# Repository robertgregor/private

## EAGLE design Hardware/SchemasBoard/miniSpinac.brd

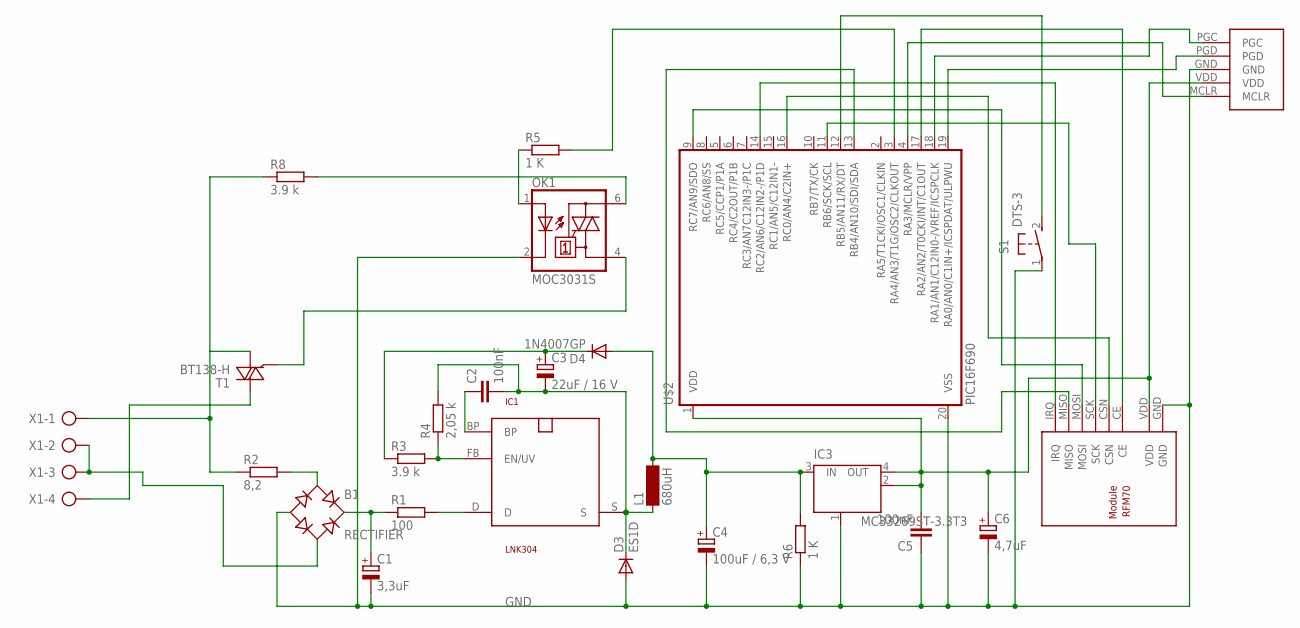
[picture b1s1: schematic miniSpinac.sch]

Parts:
B1: RECTIFIER; TO-269AA
C1: 3,3uF; E5-10,5
C2, C5: 100nF; C2012
C3: 22uF / 16 V; SMC_C
C4: 100uF / 6,3 V; E2,5-5
C6: 4,7uF; SMC_A
D3: ES1D; DO214AC
D4: 1N4007GP; DO214AA
IC1: LNK304; SO-8C
IC3: MC33269ST-3.3T3; SOT223
L1: 680uH; BS11
OK1: MOC3031S; DIL6-SMD
R1: 100; R2512W
R2: 8,2; 0411/12
R3, R8: 3.9 k; M2012
R4: 2,05 k; M2012
R5, R6: 1 K; M2012
S1: DTS-3
T1: BT138-H; TO220BH
U$1: RFM70
U$2: PIC16F690; SSOP20
U$3: PROGRAMMINGHEADERDIP; PROGHEADER
X1: AK500/4

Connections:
GND: B1.-, C1.-, C4.-, C5.1, C6.-, D3.A, IC3.1 (GND/ADJ), OK1.2 (C), R6.1, S1.1, U$1.GND, U$2.20 (VSS), U$3.GND
unnamed: IC1.D, R1.2
unnamed: B1.+, C1.+, R1.1
unnamed: B1.AC1, R2.2
unnamed: B1.AC2, X1.2, X1.3
unnamed: S1.2, U$2.12 (RB5/AN11/RX/DT)
unnamed: T1.T2 (A2), X1.4
unnamed: OK1.1 (A), R5.1
unnamed: OK1.4 (A1), T1.G
unnamed: C3.+, D4.C, R3.1
unnamed: C2.1, IC1.BP
unnamed: IC1.FB (EN/UV), R3.2, R4.1
unnamed: U$1.MISO, U$2.13 (RB4/AN10/SDI/SDA)
unnamed: C2.2, C3.-, D3.C, IC1.S, L1.1, R4.2
unnamed: OK1.6 (A2), R8.2
unnamed: U$1.CE, U$2.17 (RA2/AN2/T0CKI/INT/C1OUT)
unnamed: U$2.19 (RA0/AN0/C1IN+/ICSPDAT/ULPWU), U$3.PGD
unnamed: U$2.18 (RA1/AN1/C12IN0-/VREF/ICSPCLK), U$3.PGC
unnamed: U$1.CSN, U$2.16 (RC0/AN4/C2IN+)
unnamed: U$1.IRQ, U$2.14 (RC2/AN6/C12IN2-/P1D)
unnamed: U$1.SCK, U$2.11 (RB6/SCK/SCL)
unnamed: U$1.MOSI, U$2.9 (RC7/AN9/SDO)
unnamed: U$2.4 (RA3/MCLR/VPP), U$3.MCLR
unnamed: C4.+, D4.A, IC3.3 (IN), L1.2, R6.2
unnamed: C5.2, C6.+, IC3.2 (OUT), IC3.4 (OUT), U$1.VDD, U$2.1 (VDD), U$3.VDD
unnamed: R5.2, U$2.3 (RA4/AN3/T1G/OSC2/CLKOUT)
unnamed: R2.1, R8.1, T1.T1 (A1), X1.1

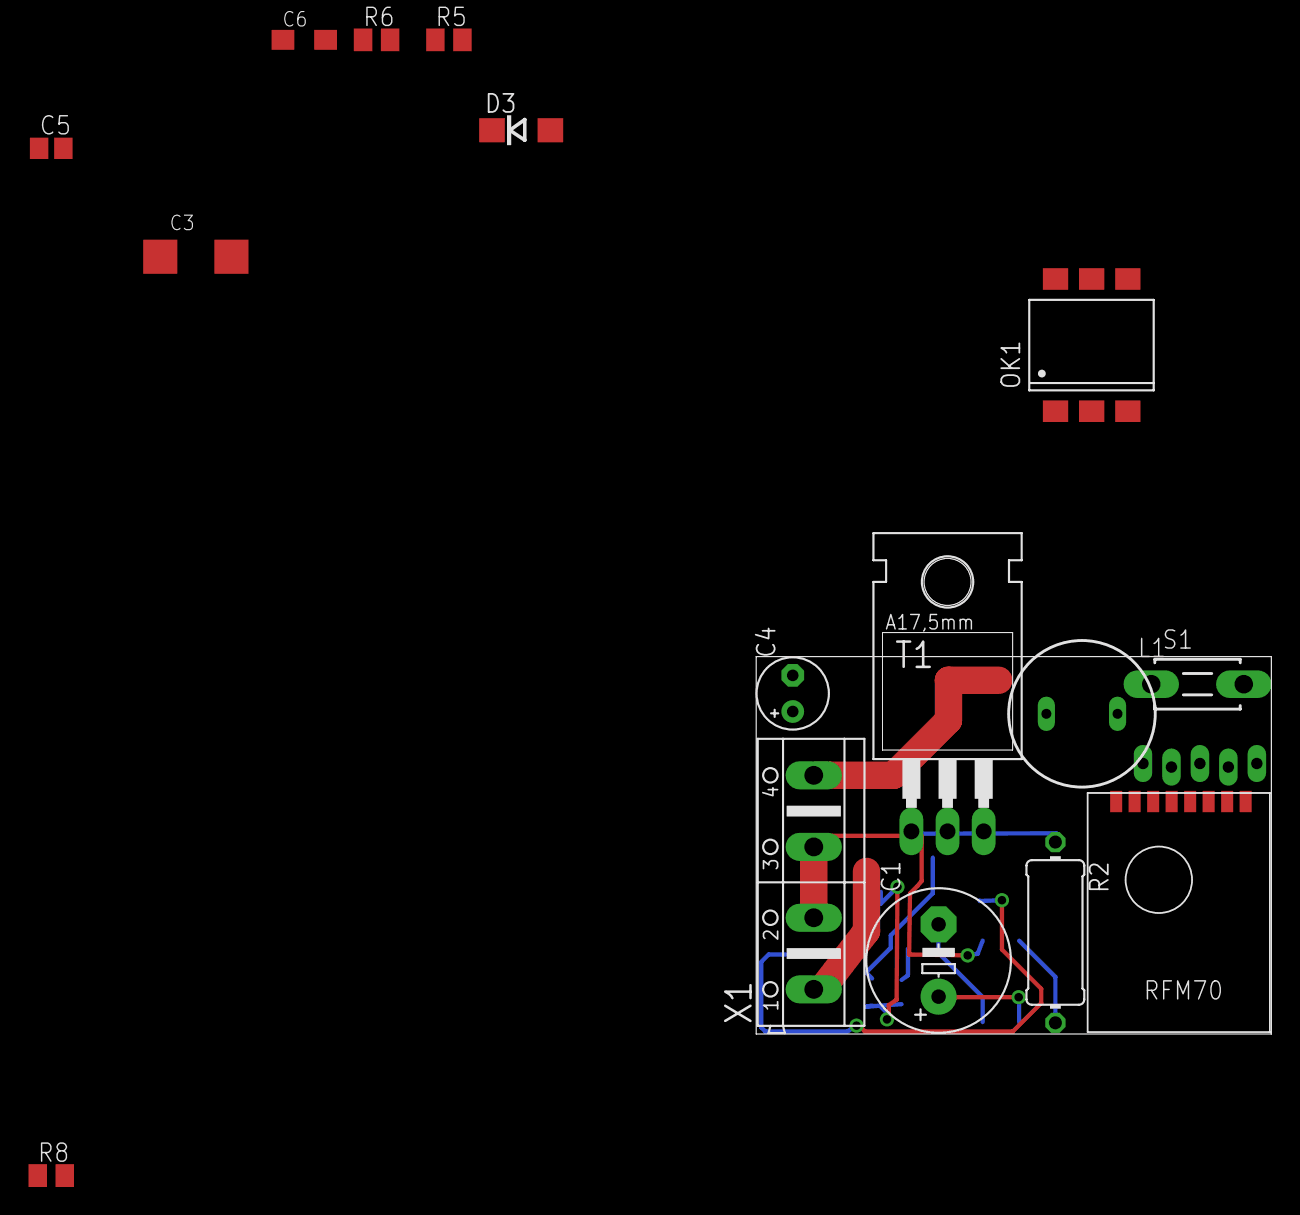
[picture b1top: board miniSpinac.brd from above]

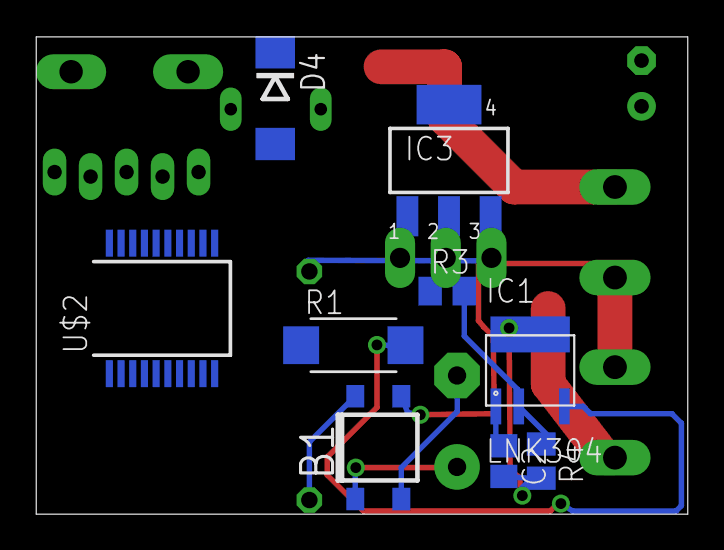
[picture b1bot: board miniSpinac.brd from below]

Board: 2 copper layers, 36.2 x 26.5 mm, 26 parts (9 on the bottom side), 27 nets.

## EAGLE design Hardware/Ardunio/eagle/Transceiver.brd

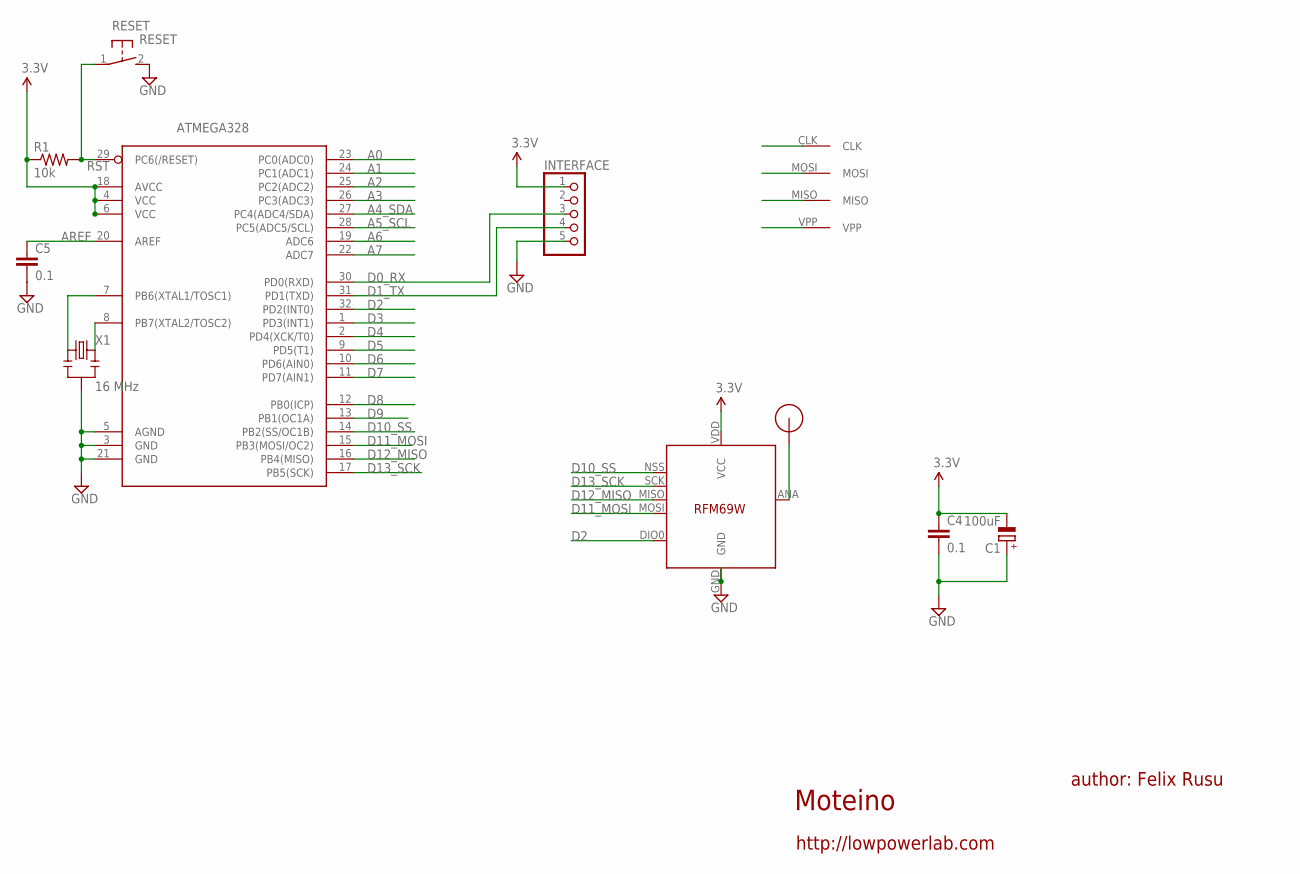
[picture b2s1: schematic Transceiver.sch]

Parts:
ATMEGA328: ATMega-328; TQFP32-08
C1: 100uF; SMC_B
C4, C5: 0.1; 0603-CAP
INTERFACE: PINHD-1X5/90; 1X05/90
R1: 10k; 0603-RES
RESET: RESET; DTSM-3
U$1: RFM12B_ANTENNA; RFM12B-ANTENNA
U$2: AVRHEADERDIP; AVRHEADER
U$5: RFM69; RFM69W-MINPADS
X1: 16 MHz; RESONATOR-SMD

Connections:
A0: ATMEGA328.23 (PC0(ADC0))
A1: ATMEGA328.24 (PC1(ADC1))
A2: ATMEGA328.25 (PC2(ADC2))
A3: ATMEGA328.26 (PC3(ADC3))
A4_SDA: ATMEGA328.27 (PC4(ADC4/SDA))
A5_SCL: ATMEGA328.28 (PC5(ADC5/SCL))
A6: ATMEGA328.19 (ADC6)
A7: ATMEGA328.22 (ADC7)
AREF: ATMEGA328.20 (AREF), C5.1
D0_RX: ATMEGA328.30 (PD0(RXD)), INTERFACE.3
D1_TX: ATMEGA328.31 (PD1(TXD)), INTERFACE.4
D2: ATMEGA328.32 (PD2(INT0)), U$5.DIO0
D3: ATMEGA328.1 (PD3(INT1))
D4: ATMEGA328.2 (PD4(XCK/T0))
D5: ATMEGA328.9 (PD5(T1))
D6: ATMEGA328.10 (PD6(AIN0))
D7: ATMEGA328.11 (PD7(AIN1))
D8: ATMEGA328.12 (PB0(ICP))
D9: ATMEGA328.13 (PB1(OC1A))
D10_SS: ATMEGA328.14 (PB2(SS/OC1B)), U$5.NSS (SEL)
D11_MOSI: ATMEGA328.15 (PB3(MOSI/OC2)), U$2.MOSI, U$5.MOSI
D12_MISO: ATMEGA328.16 (PB4(MISO)), U$2.MISO, U$5.MISO
D13_SCK: ATMEGA328.17 (PB5(SCK)), U$2.CLK, U$5.SCK
GND: ATMEGA328.3 (GND), ATMEGA328.5 (AGND), ATMEGA328.21 (GND), C1.+, C4.2, C5.2, INTERFACE.5, RESET.2, U$5.GND, X1.2
unnamed: ATMEGA328.7 (PB6(XTAL1/TOSC1)), X1.1
unnamed: U$1.P$1, U$5.ANA (ANT)
unnamed: ATMEGA328.8 (PB7(XTAL2/TOSC2)), X1.3
RST: ATMEGA328.29 (PC6(/RESET)), R1.2, RESET.1, U$2.VPP
VCC: ATMEGA328.4 (VCC), ATMEGA328.6 (VCC), ATMEGA328.18 (AVCC), C1.-, C4.1, INTERFACE.1, R1.1, U$5.VDD (VCC)

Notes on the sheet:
Moteino
author: Felix Rusu
http://lowpowerlab.com

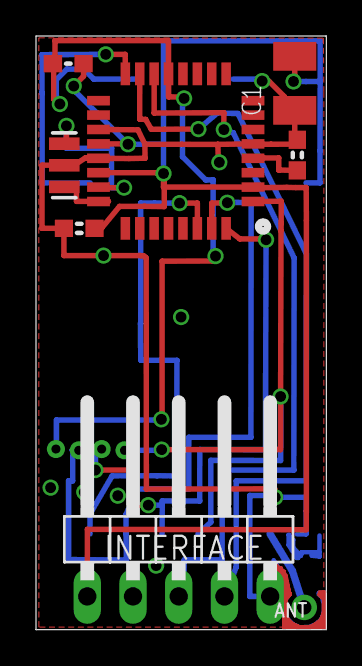
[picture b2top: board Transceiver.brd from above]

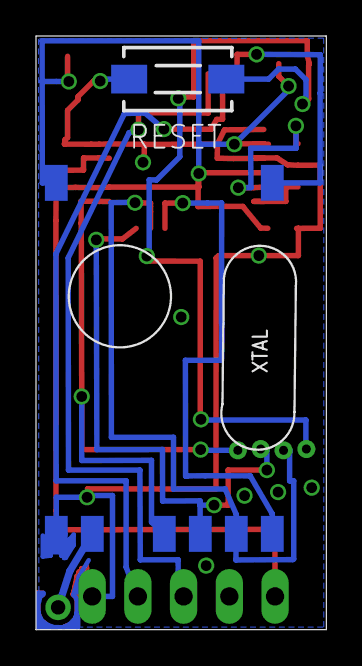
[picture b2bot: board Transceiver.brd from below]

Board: 2 copper layers, 16.1 x 33.0 mm, 11 parts (2 on the bottom side), 14 nets.

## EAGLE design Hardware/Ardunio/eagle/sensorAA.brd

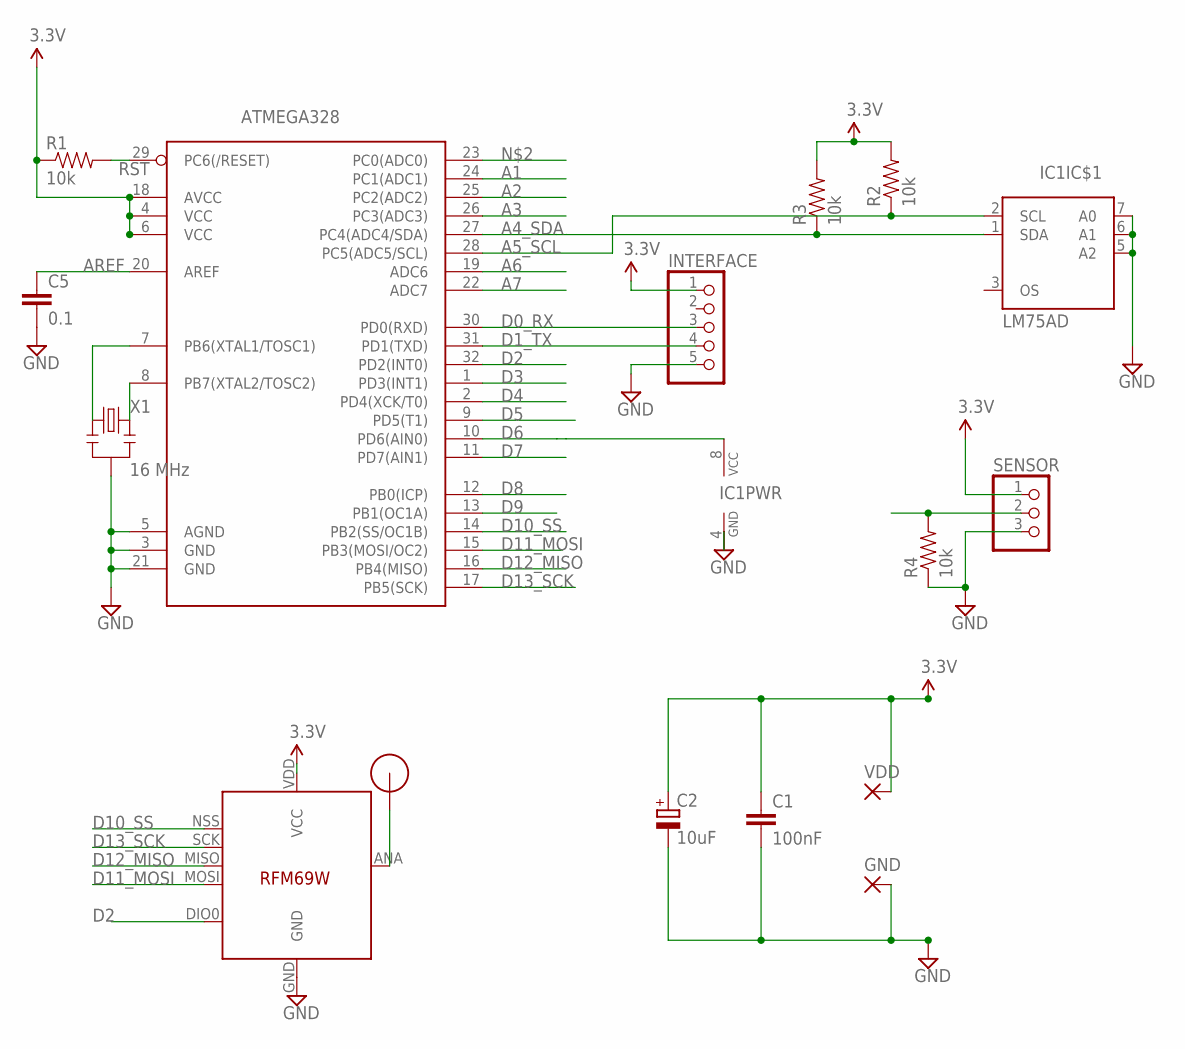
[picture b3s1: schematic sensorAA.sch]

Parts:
ATMEGA328: ATMega-328; TQFP32-08
C1: 100nF; C2012
C2: 10uF; SMC_A
C5: 0.1; 0603-CAP
GND: SMD5; SMD2,54-5,08
IC1: LM75AD; SO08
IC4: RFM69; RFM69W-MINPADS
INTERFACE: PINHD-1X5; 1X05
R1, R2, R3, R4: 10k; 0603-RES
SENSOR: PINHD-1X3; 1X03
U$1: RFM12B_ANTENNA; RFM12B-ANTENNA
VDD: SMD5; SMD2,54-5,08
X1: 16 MHz; RESONATOR-SMD

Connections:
A1: ATMEGA328.24 (PC1(ADC1))
A2: ATMEGA328.25 (PC2(ADC2))
A3: ATMEGA328.26 (PC3(ADC3))
A4_SDA: ATMEGA328.27 (PC4(ADC4/SDA)), IC1.1 (SDA), R3.1
A5_SCL: ATMEGA328.28 (PC5(ADC5/SCL)), IC1.2 (SCL), R2.1
A6: ATMEGA328.19 (ADC6)
A7: ATMEGA328.22 (ADC7)
AREF: ATMEGA328.20 (AREF), C5.1
D0_RX: ATMEGA328.30 (PD0(RXD)), INTERFACE.3
D1_TX: ATMEGA328.31 (PD1(TXD)), INTERFACE.4
D2: ATMEGA328.32 (PD2(INT0)), IC4.DIO0
D3: ATMEGA328.1 (PD3(INT1)), R4.2, SENSOR.2
D4: ATMEGA328.2 (PD4(XCK/T0))
D5: ATMEGA328.9 (PD5(T1))
D6: ATMEGA328.10 (PD6(AIN0)), IC1.8 (VCC)
D7: ATMEGA328.11 (PD7(AIN1))
D8: ATMEGA328.12 (PB0(ICP))
D9: ATMEGA328.13 (PB1(OC1A))
D10_SS: ATMEGA328.14 (PB2(SS/OC1B)), IC4.NSS (SEL)
D11_MOSI: ATMEGA328.15 (PB3(MOSI/OC2)), IC4.MOSI
D12_MISO: ATMEGA328.16 (PB4(MISO)), IC4.MISO
D13_SCK: ATMEGA328.17 (PB5(SCK)), IC4.SCK
GND: ATMEGA328.3 (GND), ATMEGA328.5 (AGND), ATMEGA328.21 (GND), C1.2, C2.-, C5.2, GND.1, IC1.4 (GND), IC1.5 (A2), IC1.6 (A1), IC1.7 (A0), IC4.GND, INTERFACE.5, R4.1, SENSOR.3, X1.2
unnamed: ATMEGA328.7 (PB6(XTAL1/TOSC1)), X1.1
unnamed: IC4.ANA (ANT), U$1.P$1
unnamed: ATMEGA328.8 (PB7(XTAL2/TOSC2)), X1.3
RST: ATMEGA328.29 (PC6(/RESET)), R1.2
VCC: ATMEGA328.4 (VCC), ATMEGA328.6 (VCC), ATMEGA328.18 (AVCC), C1.1, C2.+, IC4.VDD (VCC), INTERFACE.1, R1.1, R2.2, R3.2, SENSOR.1, VDD.1

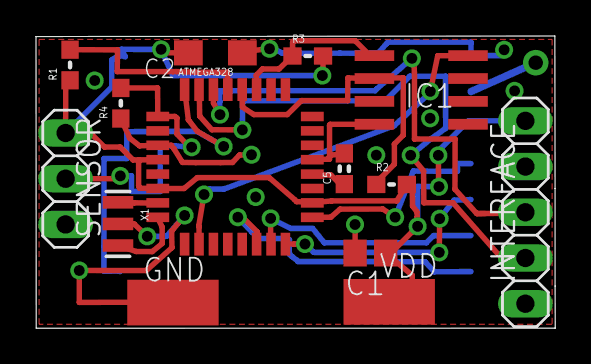
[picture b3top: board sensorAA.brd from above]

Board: 2 copper layers, 28.8 x 16.2 mm, 16 parts (1 on the bottom side), 18 nets.

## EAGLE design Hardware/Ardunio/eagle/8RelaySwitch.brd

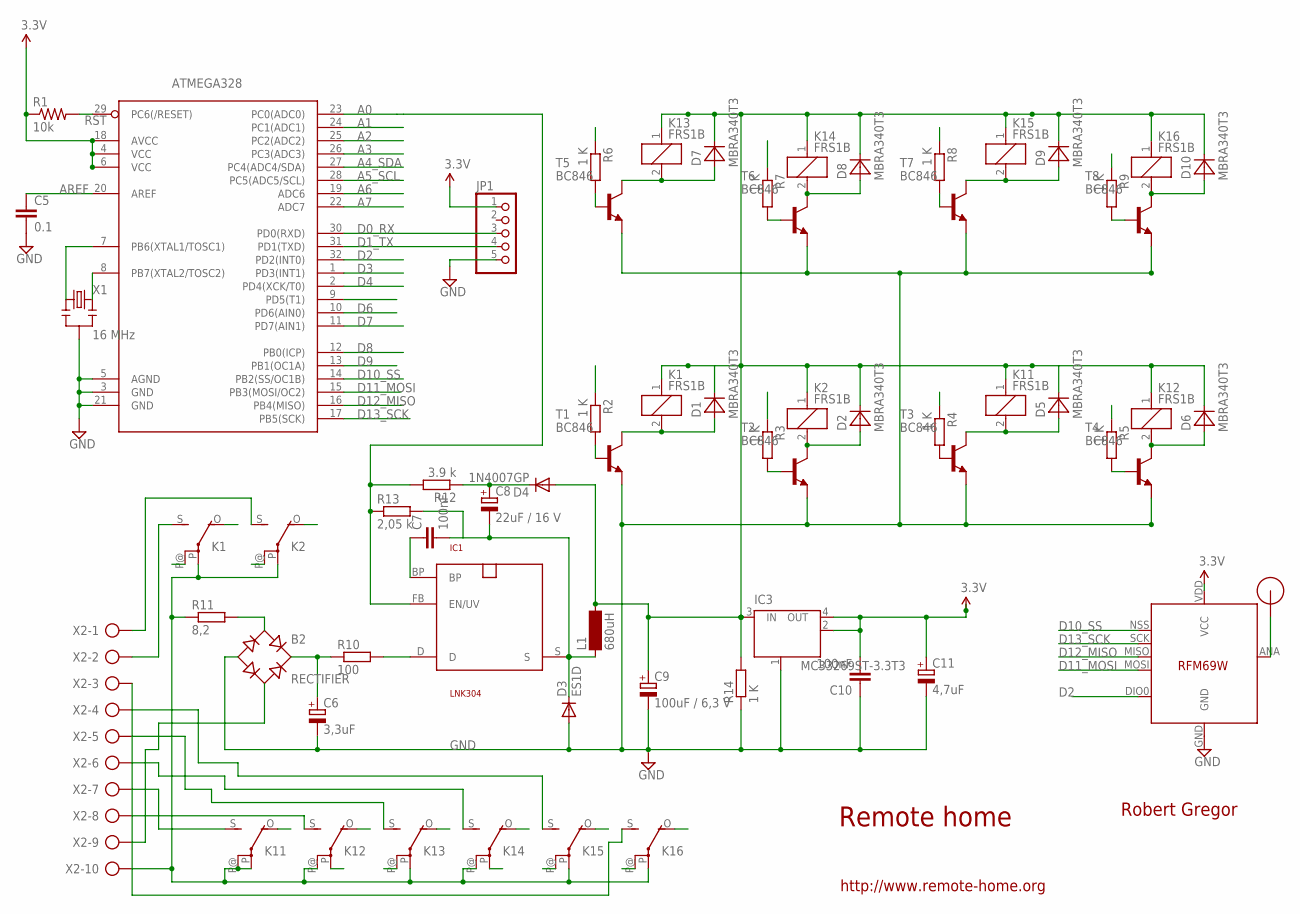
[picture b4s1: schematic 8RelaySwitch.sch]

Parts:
ATMEGA328: ATMega-328; TQFP32-08
B2: RECTIFIER; TO-269AA
C5: 0.1; 0603-CAP
C6: 3,3uF; E5-10,5
C7, C10: 100nF; C2012
C8: 22uF / 16 V; SMC_C
C9: 100uF / 6,3 V; E2,5-5
C11: 4,7uF; SMC_A
D1, D2, D5, D6, D7, D8, D9, D10: MBRA340T3; SMA
D3: ES1D; DO214AC
D4: 1N4007GP; DO214AA
IC1: LNK304; SO-8C
IC3: MC33269ST-3.3T3; SOT223
JP1: PINHD-1X5; 1X05
K1, K2, K11, K12, K13, K14, K15, K16: FRS1B
L1: 680uH; BS11
R1: 10k; 0603-RES
R2, R3, R4, R5, R6, R7, R8, R9, R14: 1 K; M2012
R10: 100; R2512W
R11: 8,2; 0411/12
R12: 3.9 k; M2012
R13: 2,05 k; M2012
T1, T2, T3, T4, T5, T6, T7, T8: BC846; SOT23
U$1: RFM12B_ANTENNA; RFM12B-ANTENNA
U$5: RFM69; RFM69W-MINPADS
X1: 16 MHz; RESONATOR-SMD
X2: AK500/10

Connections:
5V1: C9.+, D1.C, D2.C, D4.A, D5.C, D6.C, D7.C, D8.C, D9.C, D10.C, IC3.3 (IN), K1.1, K2.1, K11.1, K12.1, K13.1, K14.1, K15.1, K16.1, L1.2, R14.2
A0: ATMEGA328.23 (PC0(ADC0)), IC1.FB (EN/UV), R12.2, R13.1
A1: ATMEGA328.24 (PC1(ADC1)), R6.1
A2: ATMEGA328.25 (PC2(ADC2))
A3: ATMEGA328.26 (PC3(ADC3))
A4_SDA: ATMEGA328.27 (PC4(ADC4/SDA))
A5_SCL: ATMEGA328.28 (PC5(ADC5/SCL))
A6: ATMEGA328.19 (ADC6)
A7: ATMEGA328.22 (ADC7)
AREF: ATMEGA328.20 (AREF), C5.1
D0_RX: ATMEGA328.30 (PD0(RXD)), JP1.3
D1_TX: ATMEGA328.31 (PD1(TXD)), JP1.4
D2: ATMEGA328.32 (PD2(INT0)), U$5.DIO0
D3: ATMEGA328.1 (PD3(INT1)), R7.1
D4: ATMEGA328.2 (PD4(XCK/T0)), R8.1
D5: ATMEGA328.9 (PD5(T1)), R2.1
D6: ATMEGA328.10 (PD6(AIN0)), R3.1
D7: ATMEGA328.11 (PD7(AIN1)), R4.1
D8: ATMEGA328.12 (PB0(ICP)), R5.1
D9: ATMEGA328.13 (PB1(OC1A)), R9.1
D10_SS: ATMEGA328.14 (PB2(SS/OC1B)), U$5.NSS (SEL)
D11_MOSI: ATMEGA328.15 (PB3(MOSI/OC2)), U$5.MOSI
D12_MISO: ATMEGA328.16 (PB4(MISO)), U$5.MISO
D13_SCK: ATMEGA328.17 (PB5(SCK)), U$5.SCK
GND: ATMEGA328.3 (GND), ATMEGA328.5 (AGND), ATMEGA328.21 (GND), B2.-, C5.2, C6.-, C9.-, C10.1, C11.-, D3.A, IC3.1 (GND/ADJ), JP1.5, R14.1, T1.2 (E), T2.2 (E), T3.2 (E), T4.2 (E), T5.2 (E), T6.2 (E), T7.2 (E), T8.2 (E), U$5.GND, X1.2
unnamed: ATMEGA328.7 (PB6(XTAL1/TOSC1)), X1.1
unnamed: R2.2, T1.1 (B)
unnamed: U$1.P$1, U$5.ANA (ANT)
unnamed: D2.A, K2.2, T2.3 (C)
unnamed: D1.A, K1.2, T1.3 (C)
unnamed: R3.2, T2.1 (B)
unnamed: K1.S, X2.2
unnamed: B2.AC2, X2.9
unnamed: C7.2, C8.-, D3.C, IC1.S, L1.1, R13.2
unnamed: IC1.D, R10.2
unnamed: B2.+, C6.+, R10.1
unnamed: B2.AC1, R11.2
unnamed: C7.1, IC1.BP
unnamed: C8.+, D4.C, R12.1
unnamed: ATMEGA328.8 (PB7(XTAL2/TOSC2)), X1.3
unnamed: D5.A, K11.2, T3.3 (C)
unnamed: R4.2, T3.1 (B)
unnamed: D6.A, K12.2, T4.3 (C)
unnamed: R5.2, T4.1 (B)
unnamed: D7.A, K13.2, T5.3 (C)
unnamed: R6.2, T5.1 (B)
unnamed: D8.A, K14.2, T6.3 (C)
unnamed: R7.2, T6.1 (B)
unnamed: D9.A, K15.2, T7.3 (C)
unnamed: R8.2, T7.1 (B)
unnamed: D10.A, K16.2, T8.3 (C)
unnamed: R9.2, T8.1 (B)
unnamed: K12.S, X2.8
unnamed: K11.S, X2.7
unnamed: K1.P, K2.P, K11.P, K11.P@, K12.P@, K13.P, K14.P@, K15.P, K16.P, R11.1, X2.10
unnamed: K16.S, X2.3
unnamed: K2.S, X2.1
unnamed: K13.S, X2.5
unnamed: K14.S, X2.6
unnamed: K15.S, X2.4
RST: ATMEGA328.29 (PC6(/RESET)), R1.2
VCC: ATMEGA328.4 (VCC), ATMEGA328.6 (VCC), ATMEGA328.18 (AVCC), C10.2, C11.+, IC3.2 (OUT), IC3.4 (OUT), JP1.1, R1.1, U$5.VDD (VCC)

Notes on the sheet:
Remote home
Robert Gregor
http://www.remote-home.org

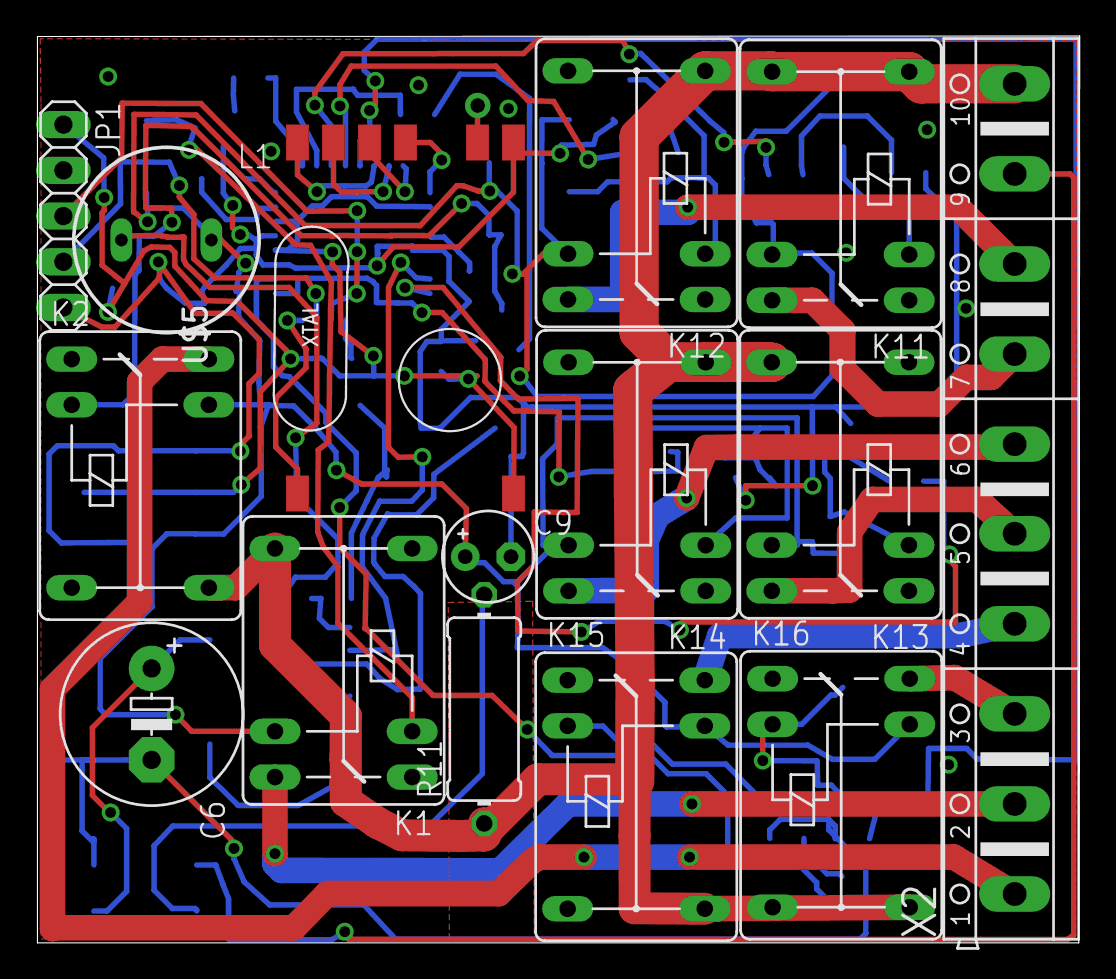
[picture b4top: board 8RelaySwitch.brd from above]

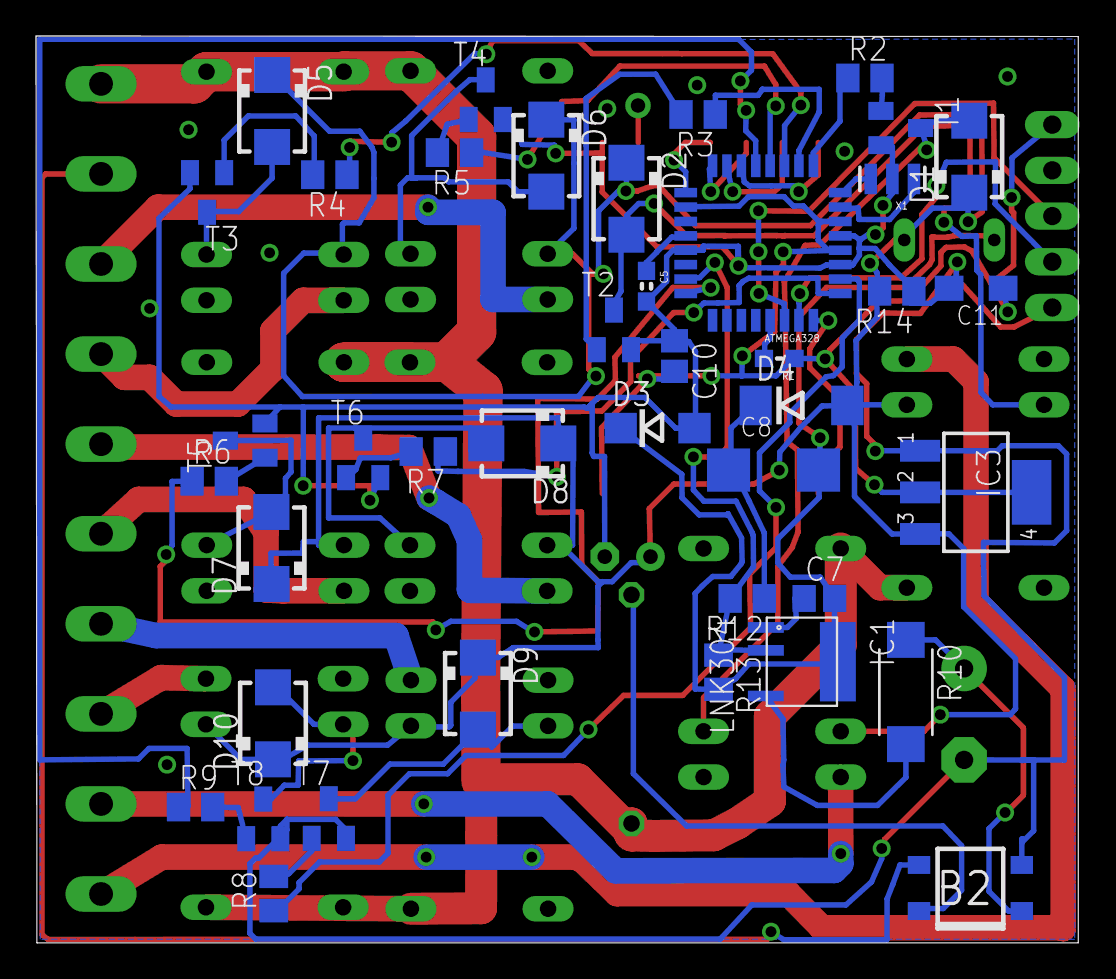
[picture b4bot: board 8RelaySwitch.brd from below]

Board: 2 copper layers, 57.9 x 50.4 mm, 57 parts (41 on the bottom side), 56 nets.

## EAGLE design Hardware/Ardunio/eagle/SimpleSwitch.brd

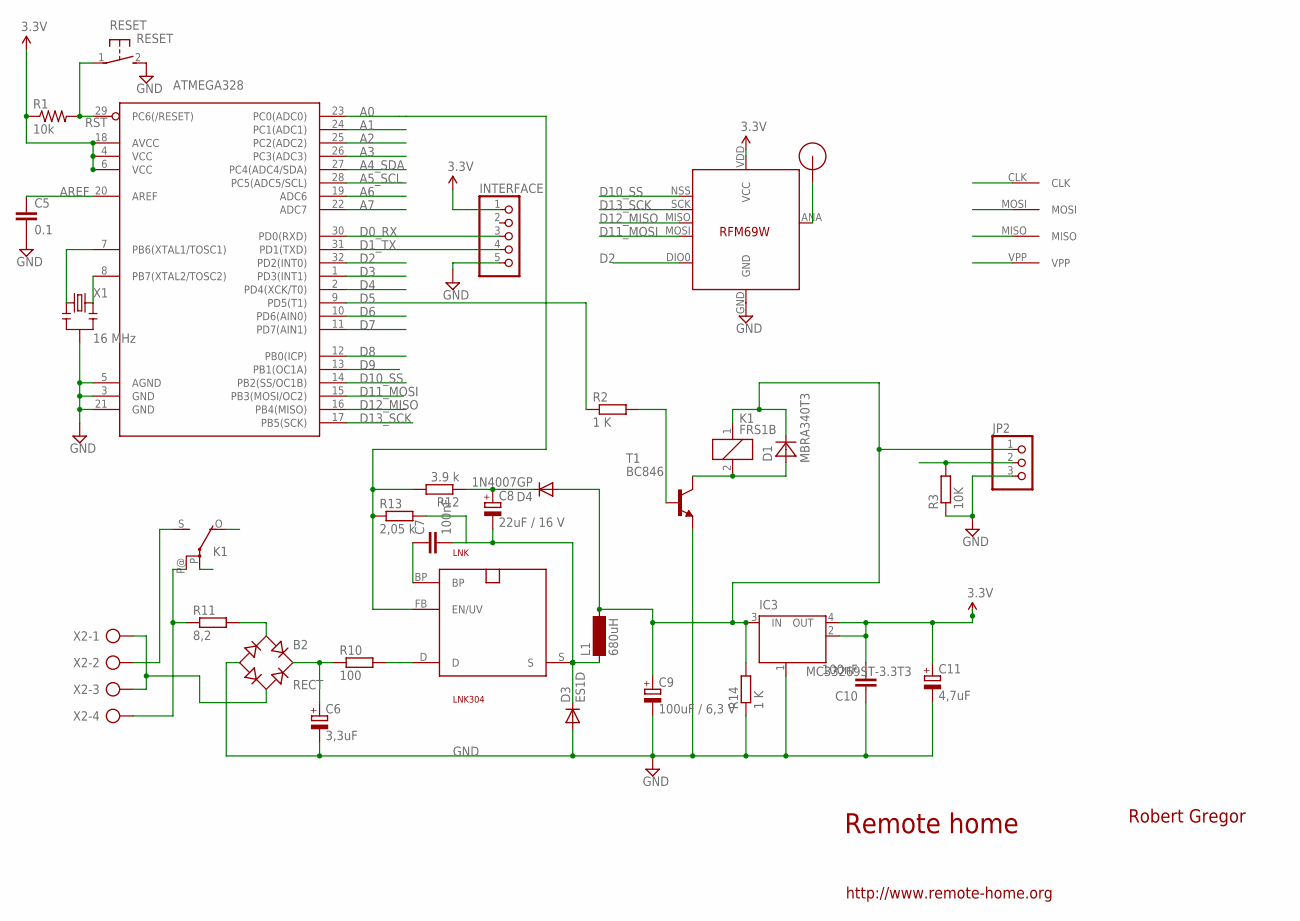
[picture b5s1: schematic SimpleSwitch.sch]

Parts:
ATMEGA328: ATMega-328; TQFP32-08
B2: RECT; TO-269AA
C5: 0.1; 0603-CAP
C6: 3,3uF; E5-10,5
C7, C10: 100nF; C2012
C8: 22uF / 16 V; SMC_C
C9: 100uF / 6,3 V; E2,5-5
C11: 4,7uF; SMC_A
D1: MBRA340T3; SMA
D3: ES1D; DO214AC
D4: 1N4007GP; DO214AA
IC3: MC33269ST-3.3T3; SOT223
INTERFACE: PINHD-1X5; 1X05
JP2: PINHD-1X3; 1X03
K1: FRS1B
L1: 680uH; BS11
LNK: LNK304; SO-8C
R1: 10k; 0603-RES
R2, R14: 1 K; M2012
R3: 10K; M2012
R10: 100; R2512W
R11: 8,2; 0411/12
R12: 3.9 k; M2012
R13: 2,05 k; M2012
RESET: RESET; DTSM-3
RFM69: RFM69; RFM69W-MINPADS
T1: BC846; SOT23
U$1: RFM12B_ANTENNA; RFM12B-ANTENNA
U$2: AVRHEADERDIP; AVRHEADER
X1: 16 MHz; RESONATOR-SMD
X2: AK500/4

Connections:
5V: C9.+, D1.C, D4.A, IC3.3 (IN), JP2.1, K1.1, L1.2, R14.2
A0: ATMEGA328.23 (PC0(ADC0)), LNK.FB (EN/UV), R12.2, R13.1
A1: ATMEGA328.24 (PC1(ADC1))
A2: ATMEGA328.25 (PC2(ADC2))
A3: ATMEGA328.26 (PC3(ADC3))
A4_SDA: ATMEGA328.27 (PC4(ADC4/SDA))
A5_SCL: ATMEGA328.28 (PC5(ADC5/SCL))
A6: ATMEGA328.19 (ADC6)
A7: ATMEGA328.22 (ADC7)
AREF: ATMEGA328.20 (AREF), C5.1
D0_RX: ATMEGA328.30 (PD0(RXD)), INTERFACE.3
D1_TX: ATMEGA328.31 (PD1(TXD)), INTERFACE.4
D2: ATMEGA328.32 (PD2(INT0)), RFM69.DIO0
D3: ATMEGA328.1 (PD3(INT1)), JP2.2, R3.2
D4: ATMEGA328.2 (PD4(XCK/T0))
D5: ATMEGA328.9 (PD5(T1)), R2.1
D6: ATMEGA328.10 (PD6(AIN0))
D7: ATMEGA328.11 (PD7(AIN1))
D8: ATMEGA328.12 (PB0(ICP))
D9: ATMEGA328.13 (PB1(OC1A))
D10_SS: ATMEGA328.14 (PB2(SS/OC1B)), RFM69.NSS (SEL)
D11_MOSI: ATMEGA328.15 (PB3(MOSI/OC2)), RFM69.MOSI, U$2.MOSI
D12_MISO: ATMEGA328.16 (PB4(MISO)), RFM69.MISO, U$2.MISO
D13_SCK: ATMEGA328.17 (PB5(SCK)), RFM69.SCK, U$2.CLK
GND: ATMEGA328.3 (GND), ATMEGA328.5 (AGND), ATMEGA328.21 (GND), B2.-, C5.2, C6.-, C9.-, C10.1, C11.-, D3.A, IC3.1 (GND/ADJ), INTERFACE.5, JP2.3, R3.1, R14.1, RESET.2, RFM69.GND, T1.2 (E), X1.2
unnamed: ATMEGA328.7 (PB6(XTAL1/TOSC1)), X1.1
unnamed: R2.2, T1.1 (B)
unnamed: RFM69.ANA (ANT), U$1.P$1
unnamed: D1.A, K1.2, T1.3 (C)
unnamed: K1.S, X2.2
unnamed: K1.P@, R11.1, X2.4
unnamed: B2.AC2, X2.1, X2.3
unnamed: C7.2, C8.-, D3.C, L1.1, LNK.S, R13.2
unnamed: LNK.D, R10.2
unnamed: B2.+, C6.+, R10.1
unnamed: B2.AC1, R11.2
unnamed: C7.1, LNK.BP
unnamed: C8.+, D4.C, R12.1
unnamed: ATMEGA328.8 (PB7(XTAL2/TOSC2)), X1.3
RST: ATMEGA328.29 (PC6(/RESET)), R1.2, RESET.1, U$2.VPP
VCC: ATMEGA328.4 (VCC), ATMEGA328.6 (VCC), ATMEGA328.18 (AVCC), C10.2, C11.+, IC3.2 (OUT), IC3.4 (OUT), INTERFACE.1, R1.1, RFM69.VDD (VCC)

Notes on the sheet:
Remote home
Robert Gregor
http://www.remote-home.org

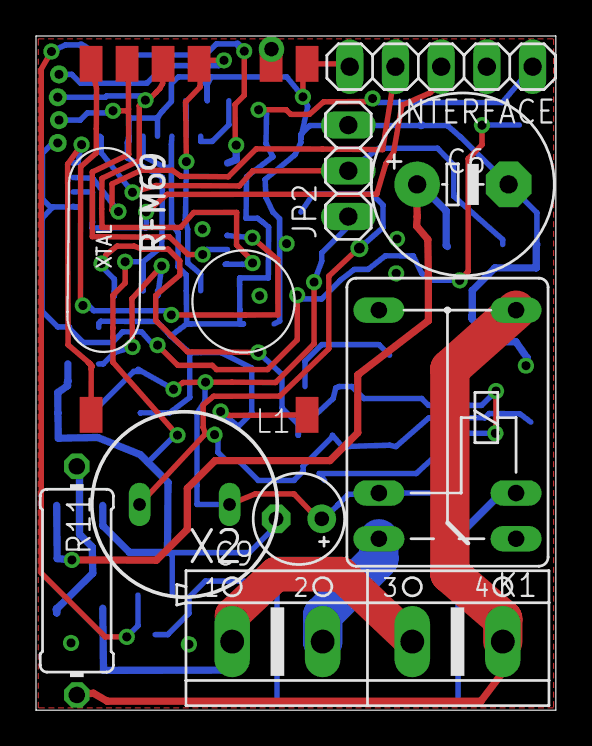
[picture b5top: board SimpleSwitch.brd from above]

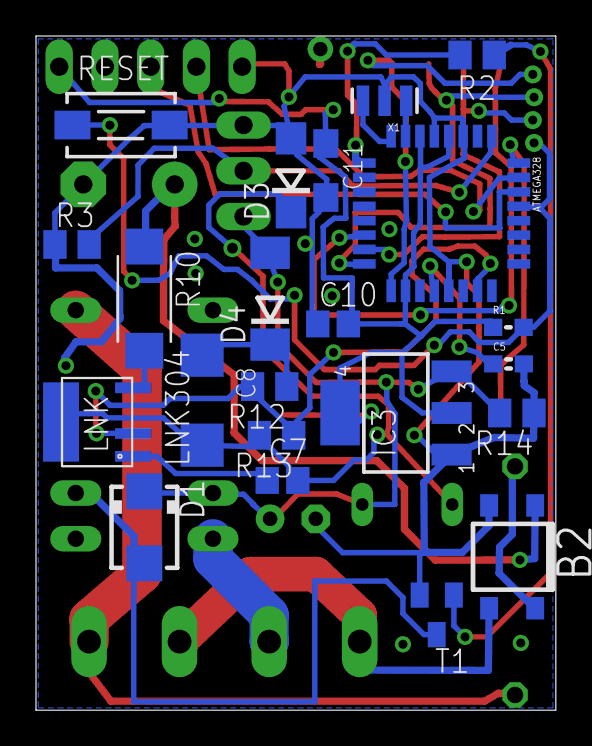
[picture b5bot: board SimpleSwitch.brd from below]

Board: 2 copper layers, 28.9 x 37.5 mm, 33 parts (22 on the bottom side), 29 nets.

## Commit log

2012-11-21 README init file..
2012-11-22 Test
2012-11-22 Merge remote-tracking branch 'origin/master'
    Conflicts:
    README
2012-11-22 Initial version of files
2012-11-22 removed test
2012-11-22 HeatingHeader finished
2012-11-22 Initial Dir structure
2012-11-23 initial version
2012-11-23 fixed bugs in displaying valve status
2012-11-23 Fine tuning
2012-11-26 Updated sources
2012-11-27 etrete
2012-11-27 back
2012-11-28 added - tunning
2012-12-04 1 st version
2012-12-05 1st version
2012-12-06 asdf
2012-12-07 renamed
2012-12-07 added
2012-12-07 connected
2012-12-14 Python API
2012-12-14 hgjk
2012-12-27 Push Test
2013-01-15 Latest final designs
2013-01-15 deleted final designs
2013-01-28 added support for remote IR detector
2013-01-31 Implement serialization functionality
2013-02-01 added persistency
2013-02-06 add switch tact
2013-02-22 asda
2013-02-25 Demo jQuery UI
2013-02-26 fdsf
2013-03-14 New version
2013-03-15 \zxcv
2013-04-09 aaaa
2013-04-10 abcd
2013-04-18 fixed power supply 22 uF C3 and differend FW diode
2013-05-02 delete
2013-05-02 dfhg
2013-05-03 sdfg
2013-05-07 safd
2013-05-08 Remove obsolete stuff
2013-05-09 fghf
2013-05-11 Maven src
2013-05-12 oprava bugu: http://manager.remote-home.org/issues/19
2013-05-16 asdas
2013-05-18 Migrate to Maven.
2013-05-18 nrjavaserial
2013-05-20 Removed old stuff
2013-05-20 removed unecessary stuff
2013-05-21 Add library
2013-05-21 Rewrite to SerialPort
2013-05-21 Run the project via maven command: mvn exec:java
2013-05-21 fixed slow scheduler selection
2013-05-22 Removed unecessary imports + comments
2013-05-22 changed parameters
2013-05-23 Vizitky
2013-05-23 Template
2013-05-23 added persistence for schedulers
2013-05-25 added update schedule
2013-05-26 Docs
2013-06-16 added thermostat components + schedulers
2013-07-30 GUI improvement - internationalisation
2013-08-08 Light alarm device - new look an field
2013-08-15 added the history data generator
2013-08-16 added charts
2013-08-20 fixed null pointer when start the brand new persistence without history sample.
2013-08-21 DeleteObject
2013-08-23 added set position
2013-08-24 Update main pom.
2013-08-24 Main.html updates.
2013-08-25 Updates.
2013-08-26 Logon.
2013-08-26 Logon
2013-08-29 last changes
2013-09-02 Fix.
2013-09-09 Fixed null pointer if the resource is not found.
2013-09-11 For some reason elseif doesnt exsist in the PBP compiler.
2013-09-17 Fixed multiple answers
2013-09-22 New RFM73 changes
2013-09-24 change in the layout
2013-10-01 Fixed bug
2013-10-01 fixed bug.
2013-10-10 Refactoring
2014-12-24 abcd
    abcd
2015-03-09 bugfix
